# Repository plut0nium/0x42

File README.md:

# >__0x42___

_Render generated by the [tracespace.io](https://tracespace.io/view/) site._

> **DISCLAIMER :**
> This PCB has been designed with Kicad6 and prototyped in late 2022.
> As of December 2023, I use Kicad7 and have converted the files to the new revised format.
> This is not expected to introduce any bug, but I do not offer any guarantee against it and provide the files AS-IS.
> You are therefore advised to perform an in-depth review of the design before manufacturing/assembly.

## Introduction
__0x42__ is an open-source 60% ortholinear keyboard PCB designed to fit the (_de facto_) standard 60% keyboard cases and use an ergo keycap set (1u alphas, with 1.5u modifiers and -optional- split 2u spacebars).

Heavily inspired by the [Boardwalk][boardwalk-url] (although the variety of supported layouts is much lower, see below), __0x42__ is based on a Raspberry Pi RP2040 (ARM) MCU with onboard USB-C connexion (or through a daughterboard), it allows the use of a rotary encoder and has a dedicated LED driver for in-switch backlight (monochrome).

## Features

 * MX-style switches
 * Standard 60% format
 * In-switch LED backlight using dedicated (_Lumissil_) LED driver
 * Rotary encoder
 * __No__ RGB underglow
 * USB Type-C with ESD protection _or_ USB daughterboard (through JST connector)
 * Powered by [QMK][qmk-url] (but could be ported to any other open-source MK firmware)

## Supported layouts

_Blue_ keys show some possible combinations of spacebars, _Orange_ can be replaced by rotary encoder, _Green_ are vertical (ergodox-like) 1.5u modifiers, and _Red_ are optional for HHKB-like layout.

## Keyboard cases

Please note that due to the ortholinear layout, some mounting holes on the PCB had to be moved (the 2 in the center part of the PCB), and consequently will not align with the standoffs commonly found in 60% tray-mount cases.
Only the 4 outer mounting holes are available in such situation.
This nevertheless results in a good fixation, particularly if using a switch plate, and should not be an issue for most users.

Other mounting types should not be affected.

## QMK Support

_TODO: add link to QMK repo_

## PCB Manufacturing & Assembly

### Panelization

[Kikit][kikit-url] can be used to produce a panelized PCB.

The included configuration in `0x42_panelize.json` will produce a single-board panel, i.e. adding a 10mm frame with tabs and mousebites.
This is not strictly required, but provides extra room for tooling holes, as well as order number placement.

```
kikit panelize -p 0x42_panelize.json 0x42.kicad_pcb panel/0x42_panel.kicad_pcb
```

### BOM

The schematic symbols have a "LCSC" property with LCSC/JLCPCB part # for suggested component reference.
As far as possible, JLCPCB _basic parts_ have been selected.
Some Kicad plugins make use of this information to extract a *.CSV BOM file that can be used for assembly.

There are many alternative references for compatible NOR flash chips, with varying capacity, from 8 to 32 Mbit or even more (note that RP2040 has a limit of 128Mbit/16MB)...

### JLCPCB

The [Kicad JLCPCB Tools][kicad-jlcpcb-url] plugin has been used to produce the required files (Gerber, drill, BOM & CPL) to have the board manufactured and assembled by JLCPCB. 

Kikit can also be used for this purpose, using `kikit fab`.

## License

CC-BY-SA 4.0

## Versions

 * __Rev 2__ _(work in progress)_ is almost identical to Rev 1, with MiniMELF diodes
 * __Rev 1__ is based on Raspberry Pi RP2040 MCU
 * __Rev 0__ is the original design and was based on a STM32F072 MCU

## Credits

 * [Boardwalk][boardwalk-url] by AlexAtPanc, Shensmobile & others... main source of inspiration for this layout
 * [Ai03][ai03-url], [Acheron Project/Gondolindrim][acheron-url], [ebastler][ebastler-url] for providing excellent opensource reference designs
 * and more generaly the mech keyboard community...

<!-- Markdwon links -->
[qmk-url]: https://qmk.fm/
[boardwalk-url]: https://panc.co/boardwalk
[ai03-url]: https://github.com/ai03-2725
[acheron-url]: https://github.com/AcheronProject
[ebastler-url]: https://github.com/ebastler
[kikit-url]: https://yaqwsx.github.io/KiKit/
[kicad-jlcpcb-url]: https://github.com/Bouni/kicad-jlcpcb-tools

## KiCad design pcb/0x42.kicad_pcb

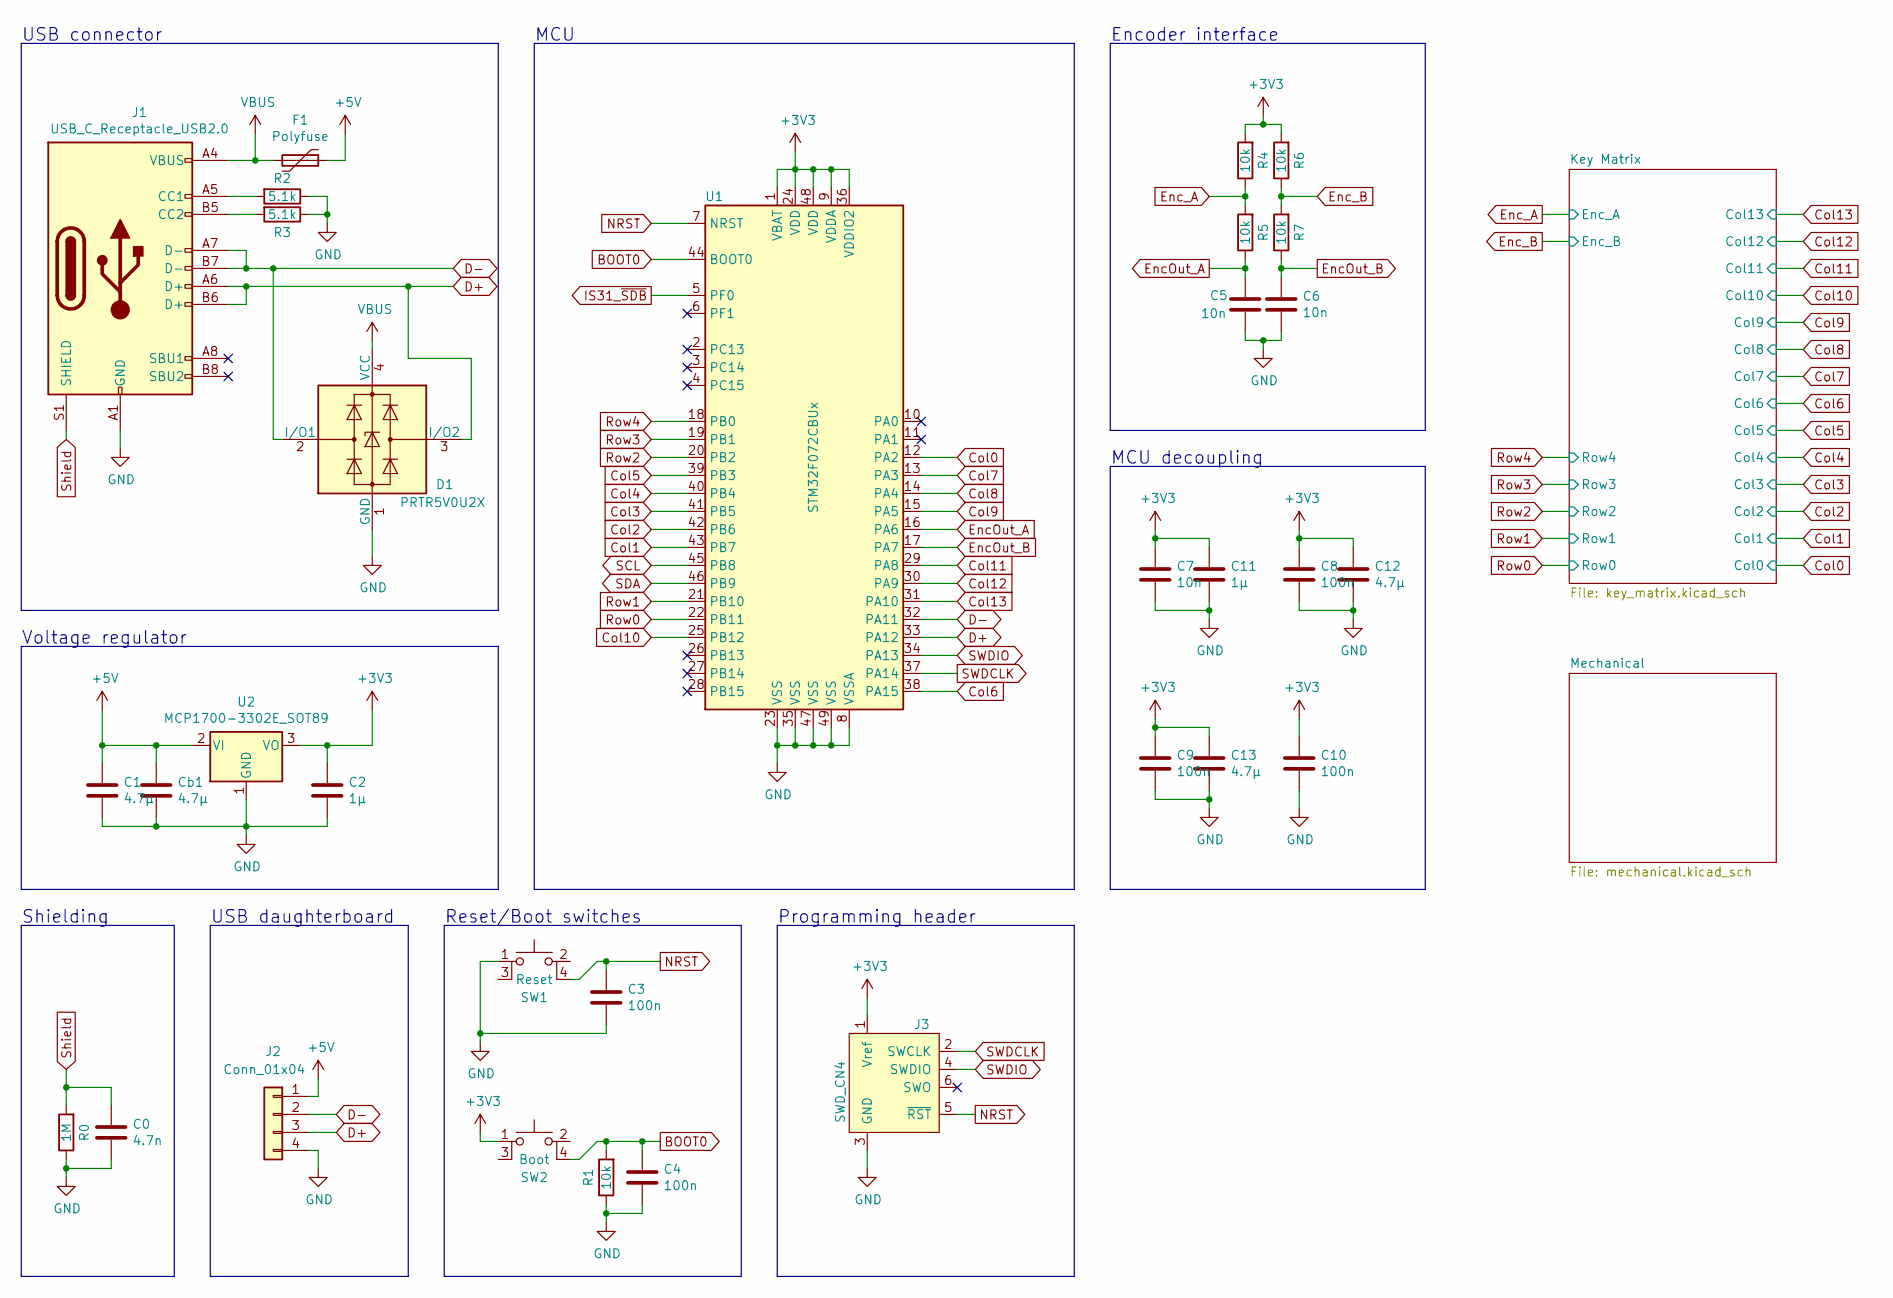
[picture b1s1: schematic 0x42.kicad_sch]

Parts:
C0: 4.7n; C_0805_2012Metric
C1: 4.7µ; C_0805_2012Metric
C2, C11: 1µ; C_0603_1608Metric
C3, C4, C8, C9, C10: 100n; C_0603_1608Metric
C5, C6, C7: 10n; C_0603_1608Metric
C12, C13: 4.7µ; C_0603_1608Metric
Cb1: 4.7µ; C_0805_2012Metric
D1: PRTR5V0U2X; SOT-143
F1: Polyfuse; Fuse_1206_3216Metric
J1: USB_C_Receptacle_USB2.0; USB_C_Receptacle_HRO_TYPE-C-31-M-12
J2: Conn_01x04; JST_SH_SM04B-SRSS-TB_1x04-1MP_P1.00mm_Horizontal
J3: SWD_CN4; SWD_1x06_P2.54mm_POGO
R0: 1M; R_0603_1608Metric
R1, R4, R5, R6, R7: 10k; R_0603_1608Metric
R2, R3: 5.1k; R_0603_1608Metric
SW1: Reset; TACT_SWITCH_5.2x5.2_4Pin
SW2: Boot; TACT_SWITCH_5.2x5.2_4Pin
U1: STM32F072CBUx; QFN-48-1EP_7x7mm_P0.5mm_EP5.6x5.6mm
U2: MCP1700-3302E_SOT89; SOT-89-3

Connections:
+3V3: C2.1, C7.1, C8.1, C9.1, C10.1, C11.1, C12.1, C13.1, J3.1 (Vref), R4.2, R6.2, SW2.1, U1.1 (VBAT), U1.9 (VDDA), U1.24 (VDD), U1.36 (VDDIO2), U1.48 (VDD), U2.3 (VO); also elsewhere on the board
+5V: C1.1, Cb1.1, F1.1, J2.1, U2.2 (VI); also elsewhere on the board
BOOT0: C4.1, R1.2, SW2.4, U1.44 (BOOT0)
Col0: U1.12 (PA2); also elsewhere on the board
Col1: U1.43 (PB7); also elsewhere on the board
Col2: U1.42 (PB6); also elsewhere on the board
Col3: U1.41 (PB5); also elsewhere on the board
Col4: U1.40 (PB4); also elsewhere on the board
Col5: U1.39 (PB3); also elsewhere on the board
Col6: U1.38 (PA15); also elsewhere on the board
Col7: U1.13 (PA3); also elsewhere on the board
Col8: U1.14 (PA4); also elsewhere on the board
Col9: U1.15 (PA5); also elsewhere on the board
Col10: U1.25 (PB12); also elsewhere on the board
Col11: U1.29 (PA8); also elsewhere on the board
Col12: U1.30 (PA9); also elsewhere on the board
Col13: U1.31 (PA10); also elsewhere on the board
D+: D1.3 (I/O2), J1.A6 (D+), J1.B6 (D+), J2.3, U1.33 (PA12)
D-: D1.2 (I/O1), J1.A7 (D-), J1.B7 (D-), J2.2, U1.32 (PA11)
EncOut_A: C5.1, R5.1, U1.16 (PA6)
EncOut_B: C6.1, R7.1, U1.17 (PA7)
Enc_A: R4.1, R5.2; also elsewhere on the board
Enc_B: R6.1, R7.2; also elsewhere on the board
GND: C0.2, C1.2, C2.2, C3.2, C4.2, C5.2, C6.2, C7.2, C8.2, C9.2, C10.2, C11.2, C12.2, C13.2, Cb1.2, D1.1 (GND), J1.A1 (GND), J1.A12 (GND), J1.B1 (GND), J1.B12 (GND), J2.4, J3.3 (GND), R0.1, R1.1, R2.1, R3.1, SW1.1, U1.8 (VSSA), U1.23 (VSS), U1.35 (VSS), U1.47 (VSS), U1.49 (VSS), U2.1 (GND); also elsewhere on the board
IS31_~SDB: U1.5 (PF0); also elsewhere on the board
NRST: C3.1, J3.5 (~RST), SW1.4, U1.7 (NRST)
unnamed: J1.A5 (CC1), R2.2
unnamed: J1.B5 (CC2), R3.2
RGB_DOUT: U1.28 (PB15); also elsewhere on the board
Row0: U1.22 (PB11); also elsewhere on the board
Row1: U1.21 (PB10); also elsewhere on the board
Row2: U1.20 (PB2); also elsewhere on the board
Row3: U1.19 (PB1); also elsewhere on the board
Row4: U1.18 (PB0); also elsewhere on the board
SCL: U1.45 (PB8); also elsewhere on the board
SDA: U1.46 (PB9); also elsewhere on the board
SWDCLK: J3.2 (SWCLK), U1.37 (PA14)
SWDIO: J3.4 (SWDIO), U1.34 (PA13)
Shield: C0.1, J1.S1 (SHIELD), R0.2; also elsewhere on the board
VBUS: D1.4 (VCC), F1.2, J1.A4 (VBUS), J1.A9 (VBUS), J1.B4 (VBUS), J1.B9 (VBUS)

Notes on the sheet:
USB daughterboard
Reset/Boot switches
Encoder interface
Programming header
MCU decoupling
MCU
Voltage regulator
USB connector
Shielding

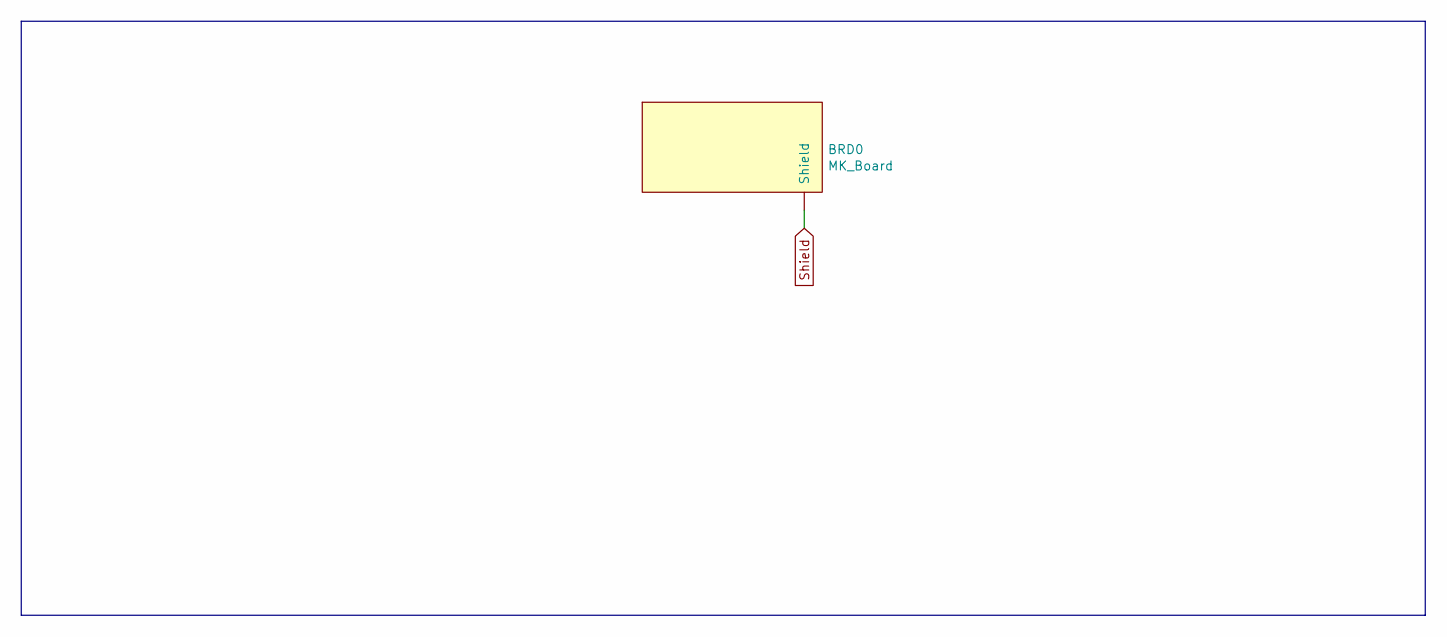
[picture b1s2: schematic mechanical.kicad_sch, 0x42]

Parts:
BRD0: MK_Board; 60_Outline_Ortho

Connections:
Shield: BRD0.1; also elsewhere on the board

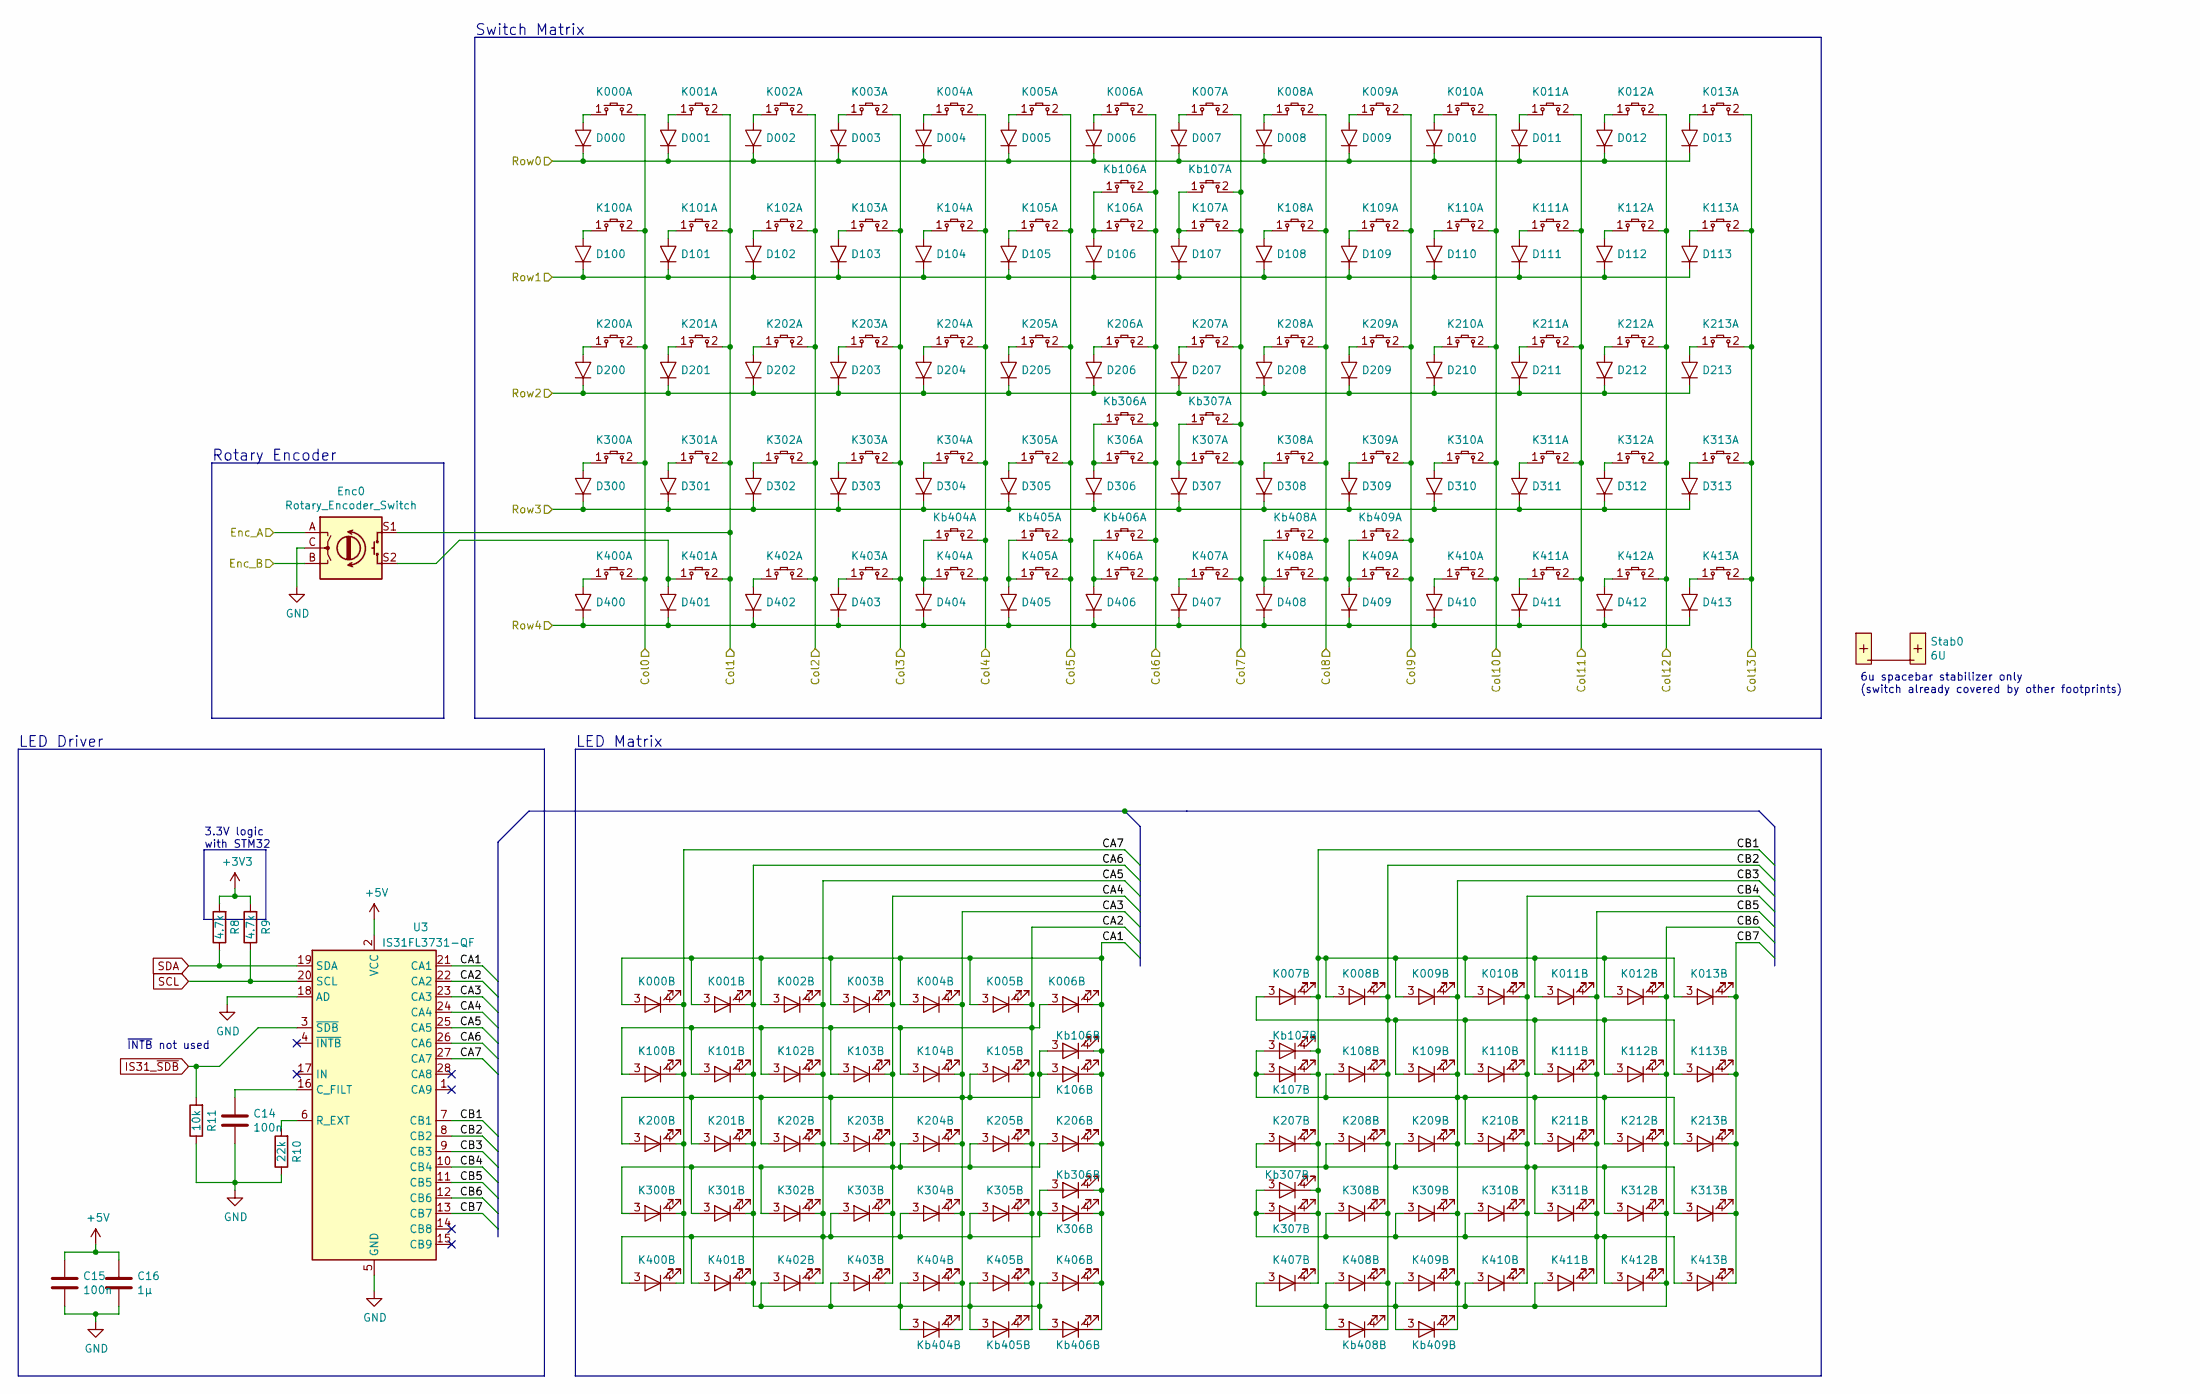
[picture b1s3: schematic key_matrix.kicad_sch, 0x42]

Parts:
C14, C15: 100n; C_0603_1608Metric
C16: 1µ; C_0603_1608Metric
D000, D001, D002, D003, D004, D005, D006, D007, D008, D009, D010, D011, D012, D013, D100, D101, D102, D103, D104, D105, D106, D107, D108, D109, D110, D111, D112, D113, D200, D201, D202, D203, D204, D205, D206, D207, D208, D209, D210, D211, D212, D213, D300, D301, D302, D303, D304, D305, D306, D307, D308, D309, D310, D311, D312, D313, D400, D401, D402, D403, D404, D405, D406, D407, D408, D409, D410, D411, D412, D413: Diode; D_SOD-323
Enc0: Rotary_Encoder_Switch; RotaryEncoder_Alps_EC11E-Switch_Vertical
K000: 1.5U; MXOnly-1.5U-Vertical-Flipped
K001, K002, K003, K004, K005, K006, K007, K008, K009, K010, K011, K012, K101, K102, K103, K104, K105, K108, K109, K110, K111, K112, K201, K202, K203, K204, K205, K206, K207, K208, K209, K210, K211, K212, K301, K302, K303, K304, K305, K306, K307, K308, K309, K310, K311, K312, K401, K402, K403, K404, K405, K406, K407, K408, K409, K410, K411, K412: 1U; MXOnly-1U
K013, K100, K113, K200, K213, K300, K313, K400, K413: 1.5U; MXOnly-1.5U
K106, K107: 1U; MXOnly-1U-Flipped
Kb106, Kb107: 1.5U; MXOnly-1.5U-Vertical
Kb306, Kb307: 1.5U; MXOnly-1.5U-Vertical-Flipped
Kb404, Kb405, Kb406, Kb408, Kb409: 2U; MXOnly-2U-ReversedStabilizers
R8, R9: 4.7k; R_0603_1608Metric
R10: 22k; R_0603_1608Metric
R11: 10k; R_0603_1608Metric
Stab0: 6U; MXOnly-6U-ReversedStabilizersOnly
U3: IS31FL3731-QF; QFN-28-1EP_4x4mm_P0.4mm_EP2.3x2.3mm

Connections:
+3V3: R8.2, R9.2; also elsewhere on the board
+5V: C15.1, C16.1, U3.2 (VCC); also elsewhere on the board
/Key Matrix/CA1: K000.3 (A), K001.3 (A), K002.3 (A), K003.3 (A), K004.3 (A), K005.3 (A), K006.4 (K), K106.4 (K), K206.4 (K), K306.4 (K), K406.4 (K), Kb106.4 (K), Kb306.4 (K), Kb406.4 (K), U3.21 (CA1)
/Key Matrix/CA2: K005.4 (K), K006.3 (A), K100.3 (A), K101.3 (A), K102.3 (A), K103.3 (A), K104.3 (A), K105.4 (K), K205.4 (K), K305.4 (K), K405.4 (K), Kb405.4 (K), U3.22 (CA2)
/Key Matrix/CA3: K004.4 (K), K104.4 (K), K105.3 (A), K106.3 (A), K200.3 (A), K201.3 (A), K202.3 (A), K203.3 (A), K204.4 (K), K304.4 (K), K404.4 (K), Kb106.3 (A), Kb404.4 (K), U3.23 (CA3)
/Key Matrix/CA4: K003.4 (K), K103.4 (K), K203.4 (K), K204.3 (A), K205.3 (A), K206.3 (A), K300.3 (A), K301.3 (A), K302.3 (A), K303.4 (K), K403.4 (K), U3.24 (CA4)
/Key Matrix/CA5: K002.4 (K), K102.4 (K), K202.4 (K), K302.4 (K), K303.3 (A), K304.3 (A), K305.3 (A), K306.3 (A), K400.3 (A), K401.3 (A), K402.4 (K), Kb306.3 (A), U3.25 (CA5)
/Key Matrix/CA6: K001.4 (K), K101.4 (K), K201.4 (K), K301.4 (K), K401.4 (K), K402.3 (A), K403.3 (A), K404.3 (A), K405.3 (A), K406.3 (A), Kb404.3 (A), Kb405.3 (A), Kb406.3 (A), U3.26 (CA6)
/Key Matrix/CA7: K000.4 (K), K100.4 (K), K200.4 (K), K300.4 (K), K400.4 (K), U3.27 (CA7)
/Key Matrix/CB1: K007.4 (K), K008.3 (A), K009.3 (A), K010.3 (A), K011.3 (A), K012.3 (A), K013.3 (A), K107.4 (K), K207.4 (K), K307.4 (K), K407.4 (K), Kb107.4 (K), Kb307.4 (K), U3.7 (CB1)
/Key Matrix/CB2: K007.3 (A), K008.4 (K), K108.4 (K), K109.3 (A), K110.3 (A), K111.3 (A), K112.3 (A), K113.3 (A), K208.4 (K), K308.4 (K), K408.4 (K), Kb408.4 (K), U3.8 (CB2)
/Key Matrix/CB3: K009.4 (K), K107.3 (A), K108.3 (A), K109.4 (K), K209.4 (K), K210.3 (A), K211.3 (A), K212.3 (A), K213.3 (A), K309.4 (K), K409.4 (K), Kb107.3 (A), Kb409.4 (K), U3.9 (CB3)
/Key Matrix/CB4: K010.4 (K), K110.4 (K), K207.3 (A), K208.3 (A), K209.3 (A), K210.4 (K), K310.4 (K), K311.3 (A), K312.3 (A), K313.3 (A), K410.4 (K), U3.10 (CB4)
/Key Matrix/CB5: K011.4 (K), K111.4 (K), K211.4 (K), K307.3 (A), K308.3 (A), K309.3 (A), K310.3 (A), K311.4 (K), K411.4 (K), K412.3 (A), K413.3 (A), Kb307.3 (A), U3.11 (CB5)
/Key Matrix/CB6: K012.4 (K), K112.4 (K), K212.4 (K), K312.4 (K), K407.3 (A), K408.3 (A), K409.3 (A), K410.3 (A), K411.3 (A), K412.4 (K), Kb408.3 (A), Kb409.3 (A), U3.12 (CB6)
/Key Matrix/CB7: K013.4 (K), K113.4 (K), K213.4 (K), K313.4 (K), K413.4 (K), U3.13 (CB7)
Col0: K000.2, K100.2, K200.2, K300.2, K400.2; also elsewhere on the board
Col1: Enc0.S1, K001.2, K101.2, K201.2, K301.2, K401.2; also elsewhere on the board
Col2: K002.2, K102.2, K202.2, K302.2, K402.2; also elsewhere on the board
Col3: K003.2, K103.2, K203.2, K303.2, K403.2; also elsewhere on the board
Col4: K004.2, K104.2, K204.2, K304.2, K404.2, Kb404.2; also elsewhere on the board
Col5: K005.2, K105.2, K205.2, K305.2, K405.2, Kb405.2; also elsewhere on the board
Col6: K006.2, K106.2, K206.2, K306.2, K406.2, Kb106.2, Kb306.2, Kb406.2; also elsewhere on the board
Col7: K007.2, K107.2, K207.2, K307.2, K407.2, Kb107.2, Kb307.2; also elsewhere on the board
Col8: K008.2, K108.2, K208.2, K308.2, K408.2, Kb408.2; also elsewhere on the board
Col9: K009.2, K109.2, K209.2, K309.2, K409.2, Kb409.2; also elsewhere on the board
Col10: K010.2, K110.2, K210.2, K310.2, K410.2; also elsewhere on the board
Col11: K011.2, K111.2, K211.2, K311.2, K411.2; also elsewhere on the board
Col12: K012.2, K112.2, K212.2, K312.2, K412.2; also elsewhere on the board
Col13: K013.2, K113.2, K213.2, K313.2, K413.2; also elsewhere on the board
Enc_A: Enc0.A; also elsewhere on the board
Enc_B: Enc0.B; also elsewhere on the board
GND: C14.2, C15.2, C16.2, Enc0.C, R10.1, R11.1, U3.5 (GND), U3.18 (AD), U3.29 (GND); also elsewhere on the board
IS31_~SDB: R11.2, U3.3 (~SDB); also elsewhere on the board
unnamed: C14.1, U3.16 (C_FILT)
unnamed: D000.2 (A), K000.1
unnamed: D001.2 (A), K001.1
unnamed: D002.2 (A), K002.1
unnamed: D003.2 (A), K003.1
unnamed: D004.2 (A), K004.1
unnamed: D005.2 (A), K005.1
unnamed: D006.2 (A), K006.1
unnamed: D007.2 (A), K007.1
unnamed: D008.2 (A), K008.1
unnamed: D009.2 (A), K009.1
unnamed: D010.2 (A), K010.1
unnamed: D011.2 (A), K011.1
unnamed: D012.2 (A), K012.1
unnamed: D013.2 (A), K013.1
unnamed: D100.2 (A), K100.1
unnamed: D101.2 (A), K101.1
unnamed: D102.2 (A), K102.1
unnamed: D103.2 (A), K103.1
unnamed: D104.2 (A), K104.1
unnamed: D105.2 (A), K105.1
unnamed: D106.2 (A), K106.1, Kb106.1
unnamed: D107.2 (A), K107.1, Kb107.1
unnamed: D108.2 (A), K108.1
unnamed: D109.2 (A), K109.1
unnamed: D110.2 (A), K110.1
unnamed: D111.2 (A), K111.1
unnamed: D112.2 (A), K112.1
unnamed: D113.2 (A), K113.1
unnamed: D200.2 (A), K200.1
unnamed: D201.2 (A), K201.1
unnamed: D202.2 (A), K202.1
unnamed: D203.2 (A), K203.1
unnamed: D204.2 (A), K204.1
unnamed: D205.2 (A), K205.1
unnamed: D206.2 (A), K206.1
unnamed: D207.2 (A), K207.1
unnamed: D208.2 (A), K208.1
unnamed: D209.2 (A), K209.1
unnamed: D210.2 (A), K210.1
unnamed: D211.2 (A), K211.1
unnamed: D212.2 (A), K212.1
unnamed: D213.2 (A), K213.1
unnamed: D300.2 (A), K300.1
unnamed: D301.2 (A), K301.1
unnamed: D302.2 (A), K302.1
unnamed: D303.2 (A), K303.1
unnamed: D304.2 (A), K304.1
unnamed: D305.2 (A), K305.1
unnamed: D306.2 (A), K306.1, Kb306.1
unnamed: D307.2 (A), K307.1, Kb307.1
unnamed: D308.2 (A), K308.1
unnamed: D309.2 (A), K309.1
unnamed: D310.2 (A), K310.1
unnamed: D311.2 (A), K311.1
unnamed: D312.2 (A), K312.1
unnamed: D313.2 (A), K313.1
unnamed: D400.2 (A), K400.1
unnamed: D401.2 (A), Enc0.S2, K401.1
unnamed: D402.2 (A), K402.1
unnamed: D403.2 (A), K403.1
unnamed: D404.2 (A), K404.1, Kb404.1
unnamed: D405.2 (A), K405.1, Kb405.1
unnamed: D406.2 (A), K406.1, Kb406.1
unnamed: D407.2 (A), K407.1
unnamed: D408.2 (A), K408.1, Kb408.1
unnamed: D409.2 (A), K409.1, Kb409.1
unnamed: D410.2 (A), K410.1
unnamed: D411.2 (A), K411.1
unnamed: D412.2 (A), K412.1
unnamed: D413.2 (A), K413.1
unnamed: R10.2, U3.6 (R_EXT)
Row0: D000.1 (K), D001.1 (K), D002.1 (K), D003.1 (K), D004.1 (K), D005.1 (K), D006.1 (K), D007.1 (K), D008.1 (K), D009.1 (K), D010.1 (K), D011.1 (K), D012.1 (K), D013.1 (K); also elsewhere on the board
Row1: D100.1 (K), D101.1 (K), D102.1 (K), D103.1 (K), D104.1 (K), D105.1 (K), D106.1 (K), D107.1 (K), D108.1 (K), D109.1 (K), D110.1 (K), D111.1 (K), D112.1 (K), D113.1 (K); also elsewhere on the board
Row2: D200.1 (K), D201.1 (K), D202.1 (K), D203.1 (K), D204.1 (K), D205.1 (K), D206.1 (K), D207.1 (K), D208.1 (K), D209.1 (K), D210.1 (K), D211.1 (K), D212.1 (K), D213.1 (K); also elsewhere on the board
Row3: D300.1 (K), D301.1 (K), D302.1 (K), D303.1 (K), D304.1 (K), D305.1 (K), D306.1 (K), D307.1 (K), D308.1 (K), D309.1 (K), D310.1 (K), D311.1 (K), D312.1 (K), D313.1 (K); also elsewhere on the board
Row4: D400.1 (K), D401.1 (K), D402.1 (K), D403.1 (K), D404.1 (K), D405.1 (K), D406.1 (K), D407.1 (K), D408.1 (K), D409.1 (K), D410.1 (K), D411.1 (K), D412.1 (K), D413.1 (K); also elsewhere on the board
SCL: R9.1, U3.20 (SCL); also elsewhere on the board
SDA: R8.1, U3.19 (SDA); also elsewhere on the board

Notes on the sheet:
6u spacebar stabilizer only (switch already covered by other footprints)
Rotary Encoder
3.3V logic with STM32
LED Matrix
~{INTB} not used
LED Driver
Switch Matrix

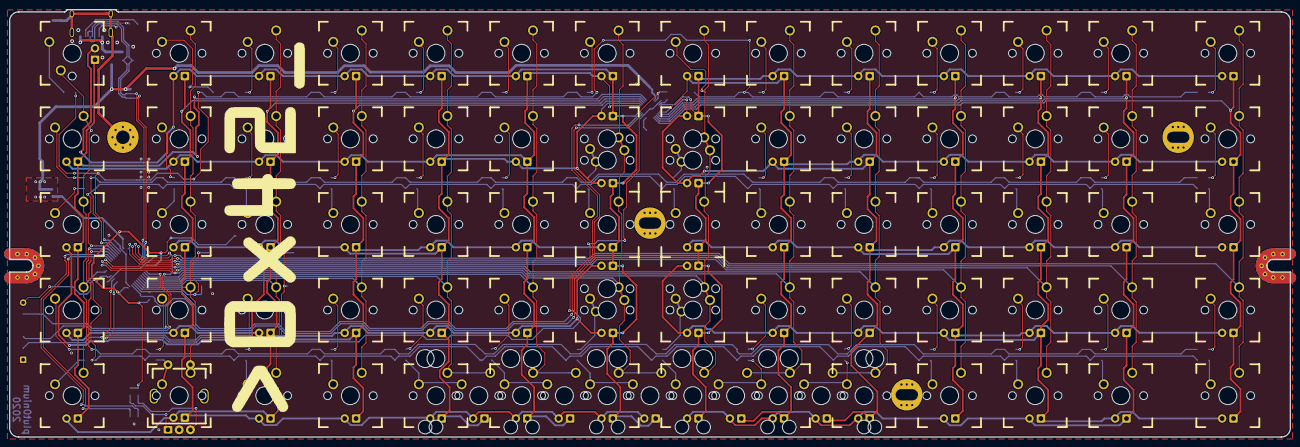
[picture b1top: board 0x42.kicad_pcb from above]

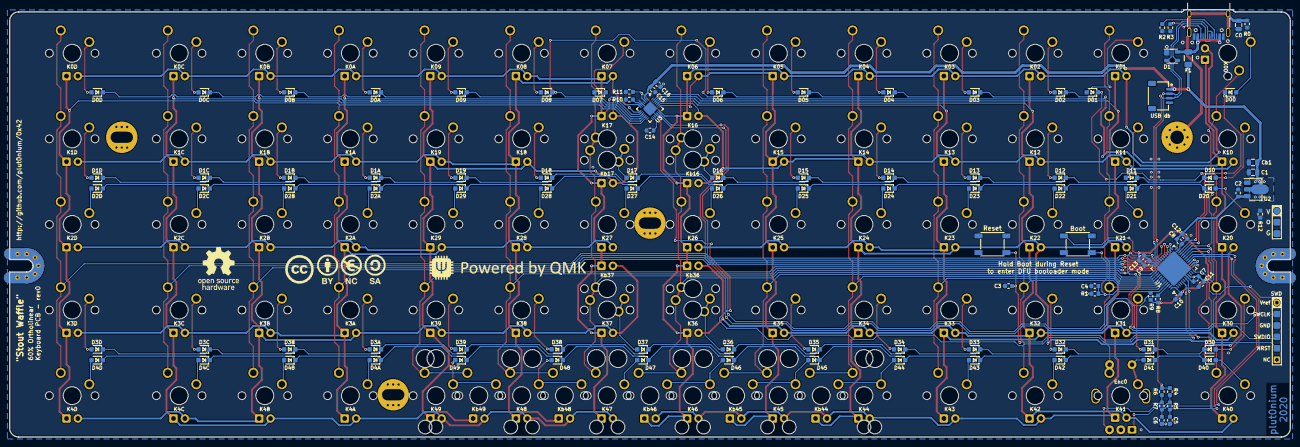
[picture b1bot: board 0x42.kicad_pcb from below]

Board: 2 copper layers, 285.0 x 95.1 mm, 194 parts (112 on the bottom side), 126 nets.

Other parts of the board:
J4: Conn_01x03; RGB_header_VoG_pads
R12: 4.7k; R_0603_1608Metric

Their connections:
+5V: J4.1, R12.2; also elsewhere on the board
GND: J4.3; also elsewhere on the board
RGB_DOUT: J4.2, R12.1; also elsewhere on the board

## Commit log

2020-06-25 Add README
2020-06-25 V1: FET driven backlight + general layout
2020-06-28 IS31 Led matrix
2020-06-28 STM32 documentation
2020-06-28 Start conversion to stm32
2020-09-03 Add doc (STM32 & ISSI)
2020-09-03 LTSpice simulation for reset circuitry
2020-09-03 Complete STM32 PCB v1
2020-09-04 Wider IS31 supply trace
2020-09-15 Replace 2x05pins SWD connector by 1x06 (Nucleo CN4 pinout)
2020-09-16 Silkscreen work
2020-09-16 Reference editing script (for Hex numbering)
2020-09-16 Script update
2020-09-16 Update Switches and Diodes references on silkscreen
2020-09-16 Ready for gerbers generation
2020-09-16 Gerbers !
2020-09-16 Documentation - README & renders
2020-10-06 README
2020-10-06 Update to 5.1.7 and PCB metadata (revision)
2020-10-06 Interactive HTML BOM
2020-10-28 README & TODO
2021-06-24 Add RGB output - WiP
2022-09-17 Switch to Kicad6
2022-09-17 Add kikit tab annotations
2022-09-29 Add Kikit panelization script
2022-09-29 PCB silkscreen work - 0x42 drawings & footprints
2022-09-29 Switched to RP2040 - PCB finalization
2022-09-29 Update documentation
2022-09-29 Minor PCB & SilkS update
2023-09-16 Panelized
2023-11-06 Convert to Kicad 7
2023-11-27 Remove outdated Rev0 html BOM
2023-12-04 Add disclaimer
2023-12-04 Remove TODO.md (outdated)
2023-12-29 remove old scripts
2023-12-29 Switch to MiniMELF (SOD-80) diodes
2023-12-29 Update/clean panelization configuration (Kikit)
2023-12-29 remove outdated panelized PCB
2023-12-30 Add kicad *.lck files to .gitignore
2023-12-30 Update BOM information
2023-12-30 Update PCB assembly information (mostly part reference numbers)
2023-12-31 solved some schematic <> pcb inconsistencies on the encoder interface
2024-01-22 Update I2C pullups + minor PCB changes
2024-01-22 Silscreen work - update license footprint
2024-01-22 Hatch infill - WARNING very slow
2024-01-22 Panelized + gerbers
2024-01-22 Add CAD files (switch plates)
2024-01-22 Add license (CC-BY-SA) text
2024-03-05 Update DoNotPopulate property for optionnal components (except switches)
2024-03-05 Bump revision number to 2.1
2024-07-05 .gitignore - exclude JLCPCBTools DB
2024-07-05 Bump to Kicad 8.0.3
2024-07-05 Alternate LCSC Part # for LL4148
2024-07-05 Hatch infill - SLOW!
2024-07-06 Minor PCB (vias) & Silkscreen
